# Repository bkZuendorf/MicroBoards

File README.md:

# CRBK-MicroBoards

In diesem Projekt werden µC-Boards bereitgestellt, die im Rahmen des Unterrichts am CRBK entstanden sind.

## Integration der Boards in die Arduino IDE
Um die Boards innerhalb der Arduino IDE nutzen zu können, müssen folgende Schritte durchgeführt werden:
- Ergänzung der Boardverwalter URL in der Arduino-IDE (unter Datei/Voreinstellungen) um die Adresse zur JSON Datei: https://raw.githubusercontent.com/bkZuendorf/MicroBoards/main/package_crbk_index.json
- Öffne in der Arduino-IDE unter Werkzeuge/Board/ den Boardverwalter
- Suche nach CRBK
- Installiere CRBK Mikrocontroller Boards

## Boards
Im Augenblick steht ein einfaches Board zur Verfügung.

### TinyRuler
Der TinyRuler ist das erste Board des CRBKs auf Basis eine ATTiny 84A. Ziel war es ein einfaches Board zum direkten Programmieren über den USB-Port zu erzeugen. Das Board ist lediglich dazu gedacht 5 LEDs abhängig von einem Lagesensor anzusprechen. Der erste Entwurf sah die Verwendung der Platinen innerhalb eines 3-D gedruckten Lineals vor. So kann mit Anheben des Lineals die Animation der LEDs verändert werden. Besonderes Augenmerk galt der energiesparenden Umsetzung der Lösung.
Das Board benötigt im Tiefschlafmodus weniger als 1µA und lässt so mit einer 200mAh Knopfzelle eine mehrmonatige Nutzung zu. 

Im Rahmen der Ausrichtung des Girls' Day wurde die Platine als Bestandteil eines Lineals vorgesehen. Das "Meldelineal" für Schülerinnen und Schüler wurde wir folgt gestaltet:

Das [Video](https://www.abitur-am-berufskolleg.info/wp-content/uploads/2021/11/TinyRuler.mp4) zeigt das geplante Aussehen in einer ersten Version.

Ein Video des fertigen Exponats folgt ...

Das [Eagle Layout](https://github.com/bkZuendorf/MicroBoards/tree/main/documentation/TinyRuler/PCB-Layout) kann verwendet werden, um die Platine nachzubauen.
Die [Fusion CAD-Datei](https://github.com/bkZuendorf/MicroBoards/tree/main/documentation/TinyRuler/Fusion-Design) dient der Erzeugung einer 3D-Druck Datei.

#### Treiber
Zur Verwendung des TinyRuler ist die Installation eines Treibers erforderlich. Dies kann entsprechend der Anleitung auf der Original-Bootloader Seite [Micronucleus](https://github.com/micronucleus/micronucleus/tree/master/windows_driver_installer) erfolgen.

#### Erstprogrammierung
Bevor das Board über die USB-Schnittstelle programmiert werden kann, muss einmalig ein Bootloader programmiert werde,
Der Bootloader muss mit einem Programmieradapter mit üblichen Mitteln (avrdude, Microchip-Studio, ...) programmiert werden. Das fertig [compiliertes Produktionsfile](https://github.com/bkZuendorf/MicroBoards/blob/main/ATTiny84_productionfile.elf) steht zur Verfügung.
Zusätzlich müssen die Fuses geändert werden:
- SELFPRGEN: enable 
- WDTON: disable (keinen Watchdog, wird nicht genutzt und benötigt im Tiefschlaf zu viel Energie)
- BODLEVEL: disable (Brown-out detection deaktiviern, damit µC auch mit geringer Spannung arbeitet)

Am Ende sollten die Fuse-Register folgende Werte haben:
- EXTENDED: 0xFE
- HIGH: 0xDF
- LOW: 0xE2

#### Programmierung
Nach Integration in die Arduino IDE (s.o.) stehen einige [Beispiele](https://github.com/bkZuendorf/MicroBoards/tree/main/CRBK-MicroBoards/libraries/TinyRuler/examples) zur Verfügung. Mit recht einfachen Mitteln können die LEDs programmiert, Animationen erzeugt werden und der µC in einen energiesparenden Modus versetzt werden.

Das untenstehende Beispiel zeigt eine typische Anwendung der TinyRuler-Bibliothek
```
#include "TinyRuler.h" // Binde den Bibliothek-Header ein

TinyRuler ruler;  // Erstelle eine Instanz des Lineals

void setup() {
  ruler.init();  // Initialisiere das Lineal bei Start des µCs 
}

void loop()
{
  bool sensor = ruler.getSensor(); // ermittelt die Linealposition, true zeigt liegende Position an

  if(sensor) {
    // Lineal liegt
    ruler.reset(0);   // schalte LED 0 aus
    ruler.toggle(1);  // wechsle den Zustand der LED 1
    delay(500);
    ruler.toggle(2);  // wechsle den Zustand der LED 2
    delay(500);
  } else {
    // Lineal liegt nicht
    if(ruler.get(1)) {
      // wenn LED 1 leuchtet, schalte alle LEDs aus
      ruler.resetAll();
    } else {
      // wenn LED 1 nicht leuchtet, schalte alle LEDs an
      ruler.setAll();
    }
    delay(50);
  }
    
  // rufe handle auf, damit der Lagezustand ermittelt werden kann und 
  // sich das Lineal nach einer Zeit schlafen legt und automatisch wieder aufwacht
  // hier: Lasse Lineal 2,5 Sekunden nach dem Erkennen der Lage in den Schlafmodus wechseln
  ruler.handle(2500);
}
```

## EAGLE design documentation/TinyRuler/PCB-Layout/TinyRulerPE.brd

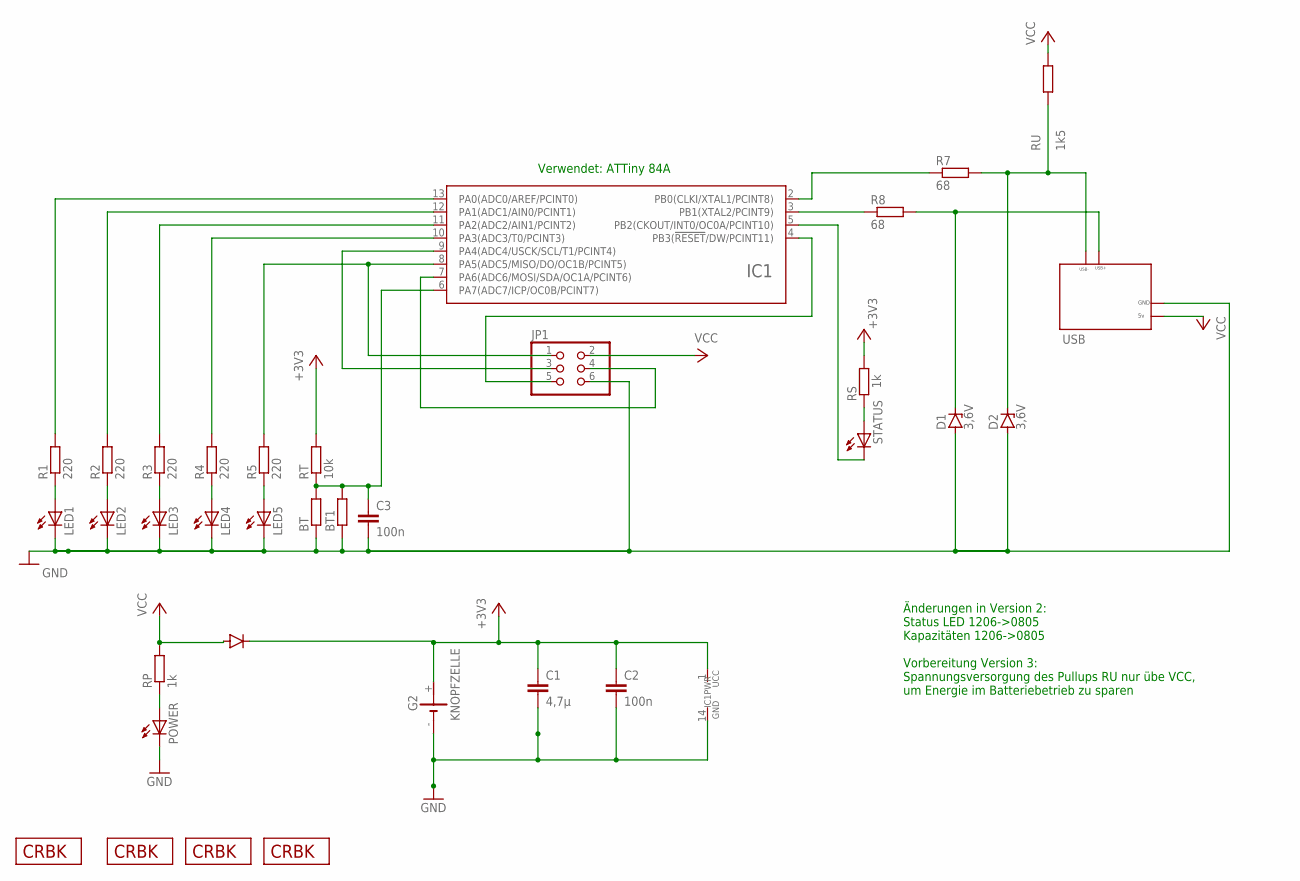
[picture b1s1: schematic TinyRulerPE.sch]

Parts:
BT: R-EU_0411/15; 0411/15
BT1: R-EU_0309/10; 0309/10
C1: 4,7µ; C0805
C2, C3: 100n; C0805
D1, D2: 3,6V; SOT23
D4: DIODE-SOD323-W; SOD323-W
G2: KNOPFZELLE; KZH20
IC1: ATTINY24/44/84-SSU; SOIC14
JP1: PINHD-2X3; 2X03
L1, L4: CRBKLOGO-2020TN_TEXT; CRBK-LOGO-2020-XS-TN-TEXT
L2, L3: CRBKLOGO-2020TN_S_BILD; CRBK-LOGO-2020-S-TN-BILD
LED1, LED2, LED3, LED4, LED5: LEDCHIPLED_1206; CHIPLED_1206
POWER: LEDCHIPLED_0805; CHIPLED_0805
R1, R2, R3, R4, R5: 220; R0805
R7, R8: 68; R0805
RP: 1k; R0805
RS: 1k; R0805
RT: 10k; R0805
RU: 1k5; R0805
STATUS: LEDCHIPLED_0805; CHIPLED_0805
USB: USBCONNECTOR

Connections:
+3V3: C1.1, C2.1, D4.C, G2.+, IC1.1 (UCC), RS.2, RT.2
GND: BT.1, BT1.1, C1.2, C2.2, C3.2, D1.1 (A), D2.1 (A), G2.-, IC1.14 (GND), JP1.6, LED1.C, LED2.C, LED3.C, LED4.C, LED5.C, POWER.C, USB.GND
unnamed: LED2.A, R2.1
unnamed: LED1.A, R1.1
unnamed: LED3.A, R3.1
unnamed: LED4.A, R4.1
unnamed: LED5.A, R5.1
unnamed: IC1.9 (PA4(ADC4/USCK/SCL/T1/PCINT4)), JP1.3
unnamed: IC1.8 (PA5(ADC5/MISO/DO/OC1B/PCINT5)), JP1.1, R5.2
unnamed: IC1.13 (PA0(ADC0/AREF/PCINT0)), R1.2
unnamed: IC1.4 (PB3(!RESET!/DW/PCINT11)), JP1.5
unnamed: BT.2, BT1.2, C3.1, IC1.6 (PA7(ADC7/ICP/OC0B/PCINT7)), RT.1
unnamed: IC1.12 (PA1(ADC1/AIN0/PCINT1)), R2.2
unnamed: D1.3 (C), R8.2, USB.USB+
unnamed: D2.3 (C), R7.2, RU.1, USB.USB-
unnamed: IC1.11 (PA2(ADC2/AIN1/PCINT2)), R3.2
unnamed: POWER.A, RP.1
unnamed: IC1.5 (PB2(CKOUT/INT0/OC0A/PCINT10)), STATUS.C
unnamed: IC1.7 (PA6(ADC6/MOSI/SDA/OC1A/PCINT6)), JP1.4
unnamed: RS.1, STATUS.A
unnamed: IC1.10 (PA3(ADC3/T0/PCINT3)), R4.2
unnamed: IC1.2 (PB0(CLKI/XTAL1/PCINT8)), R7.1
unnamed: IC1.3 (PB1(XTAL2/PCINT9)), R8.1
VCC: D4.A, JP1.2, RP.2, RU.2, USB.+5V (5V)

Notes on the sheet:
Änderungen in Version 2: Status LED 1206->0805 Kapazitäten 1206->0805 Vorbereitung Version 3: Spannungsversorgung des Pullups RU nur übe VCC, um Energie im Batteriebetrieb zu sparen
Verwendet: ATTiny 84A

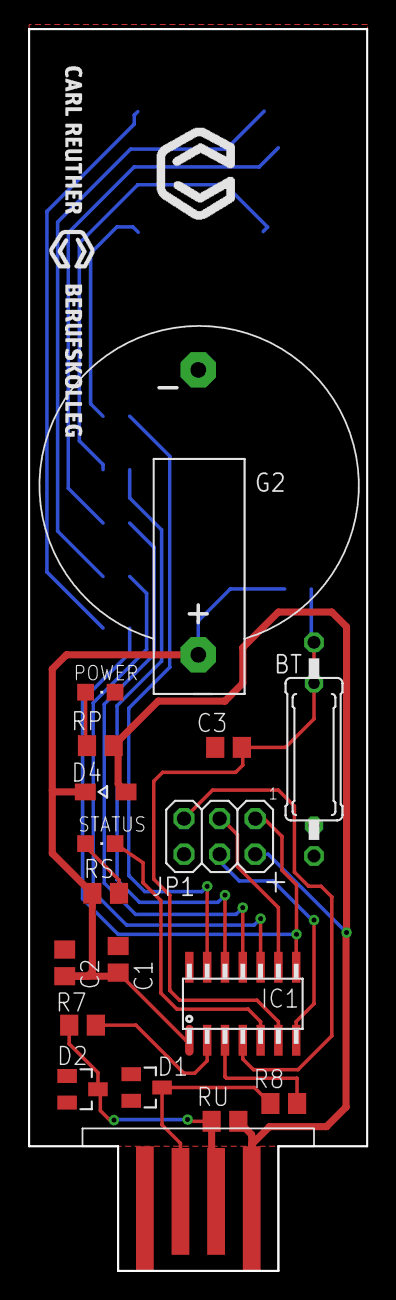
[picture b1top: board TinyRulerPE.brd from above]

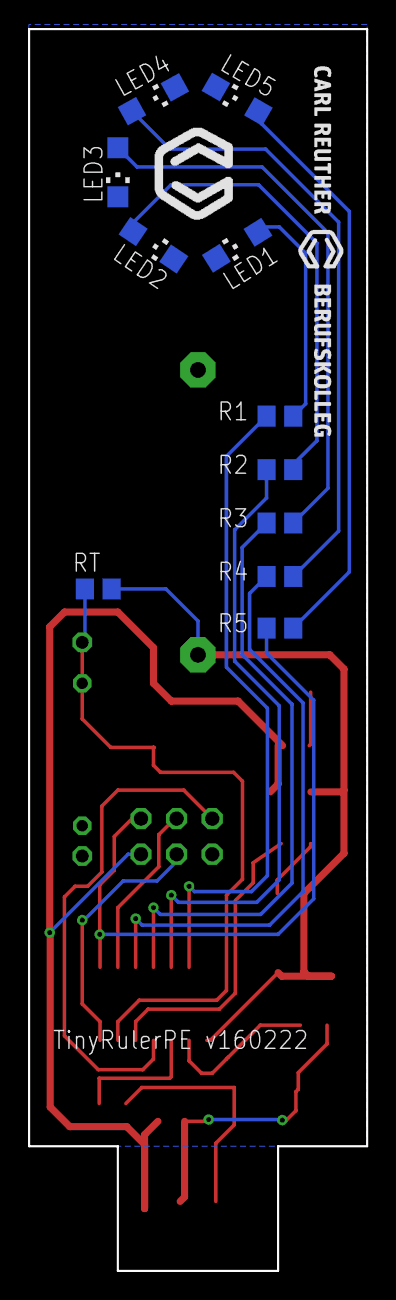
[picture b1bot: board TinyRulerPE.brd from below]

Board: 2 copper layers, 24.1 x 88.6 mm, 34 parts (13 on the bottom side), 24 nets.

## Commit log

2022-02-03 first
2022-02-03 second
2022-02-03 third
2022-02-03 fourth
2022-02-03 fifth
2022-02-03 sixth
2022-02-04 test Zweitgerät
2022-02-04 zweites Beispiel
2022-02-04 handle-Funktion zur Ŕealisierung des Schlafmodus
2022-02-04 Archivupdate
2022-02-05 nun schläft's
2022-02-06 schöneres Beispiel, toggle, get ergänzt
2022-02-06 Optimierung des Tiefschlafs
2022-02-06 Update zip-Archiv
2022-02-06 Datentypfehler behoben
2022-02-17 Optimierte Firmware zur Nutzung eines eEnergiesparenden pull-ups
2022-02-17 AD Wandler ausgeschaltet für power save deep sleep
2022-02-17 Release Paket nachgezogen
2022-02-18 Animation überarbeitet
2022-02-20 Eagle Layout ergänzt
2022-02-20 Bild ergänzt
2022-02-20 Fusion Datei ergänzt
2022-02-20 Animation überarbeitet
    Eagle Layout ergänzt
    Bild ergänzt
    Update README.md
    Fusion Datei ergänzt
2022-02-20 Create LICENSE
